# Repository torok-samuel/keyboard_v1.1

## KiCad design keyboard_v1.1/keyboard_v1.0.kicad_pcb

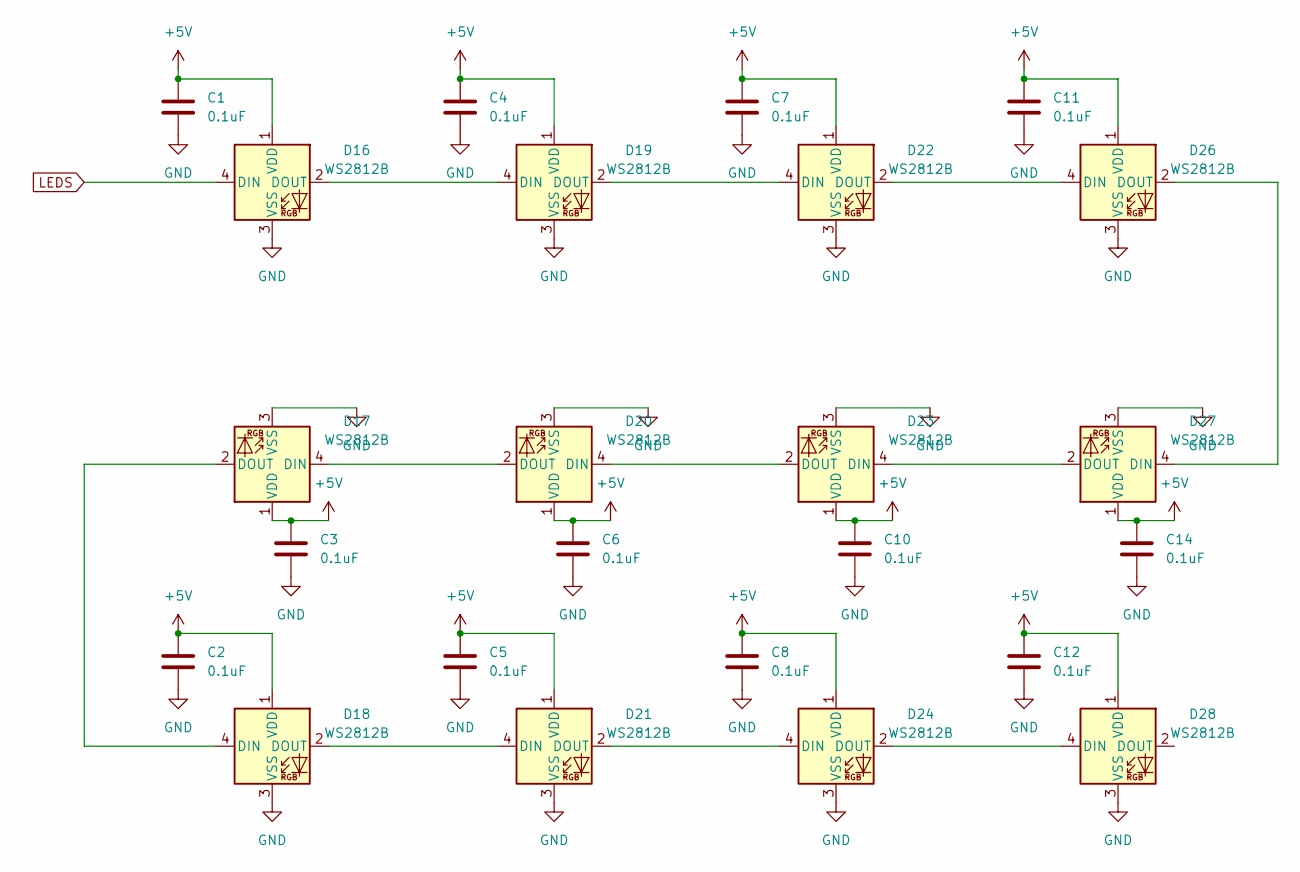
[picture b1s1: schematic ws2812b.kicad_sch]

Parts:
C1, C2, C3, C4, C5, C6, C7, C8, C10, C11, C12, C14: 0.1uF; C_0805_2012Metric_Pad1.18x1.45mm_HandSolder
D16, D17, D18, D19, D20, D21, D22, D23, D24, D26, D27, D28: WS2812B; LED_WS2812B_PLCC4_5.0x5.0mm_P3.2mm

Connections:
5V_OUT: C1.1, C2.1, C3.1, C4.1, C5.1, C6.1, C7.1, C8.1, C10.1, C11.1, C12.1, C14.1, D16.1 (VDD), D17.1 (VDD), D18.1 (VDD), D19.1 (VDD), D20.1 (VDD), D21.1 (VDD), D22.1 (VDD), D23.1 (VDD), D24.1 (VDD), D26.1 (VDD), D27.1 (VDD), D28.1 (VDD); also elsewhere on the board
GND: C1.2, C2.2, C3.2, C4.2, C5.2, C6.2, C7.2, C8.2, C10.2, C11.2, C12.2, C14.2, D16.3 (VSS), D17.3 (VSS), D18.3 (VSS), D19.3 (VSS), D20.3 (VSS), D21.3 (VSS), D22.3 (VSS), D23.3 (VSS), D24.3 (VSS), D26.3 (VSS), D27.3 (VSS), D28.3 (VSS); also elsewhere on the board
LEDS: D16.4 (DIN); also elsewhere on the board
unnamed: D16.2 (DOUT), D19.4 (DIN)
unnamed: D17.2 (DOUT), D18.4 (DIN)
unnamed: D17.4 (DIN), D20.2 (DOUT)
unnamed: D18.2 (DOUT), D21.4 (DIN)
unnamed: D19.2 (DOUT), D22.4 (DIN)
unnamed: D20.4 (DIN), D23.2 (DOUT)
unnamed: D21.2 (DOUT), D24.4 (DIN)
unnamed: D22.2 (DOUT), D26.4 (DIN)
unnamed: D23.4 (DIN), D27.2 (DOUT)
unnamed: D24.2 (DOUT), D28.4 (DIN)
unnamed: D26.2 (DOUT), D27.4 (DIN)

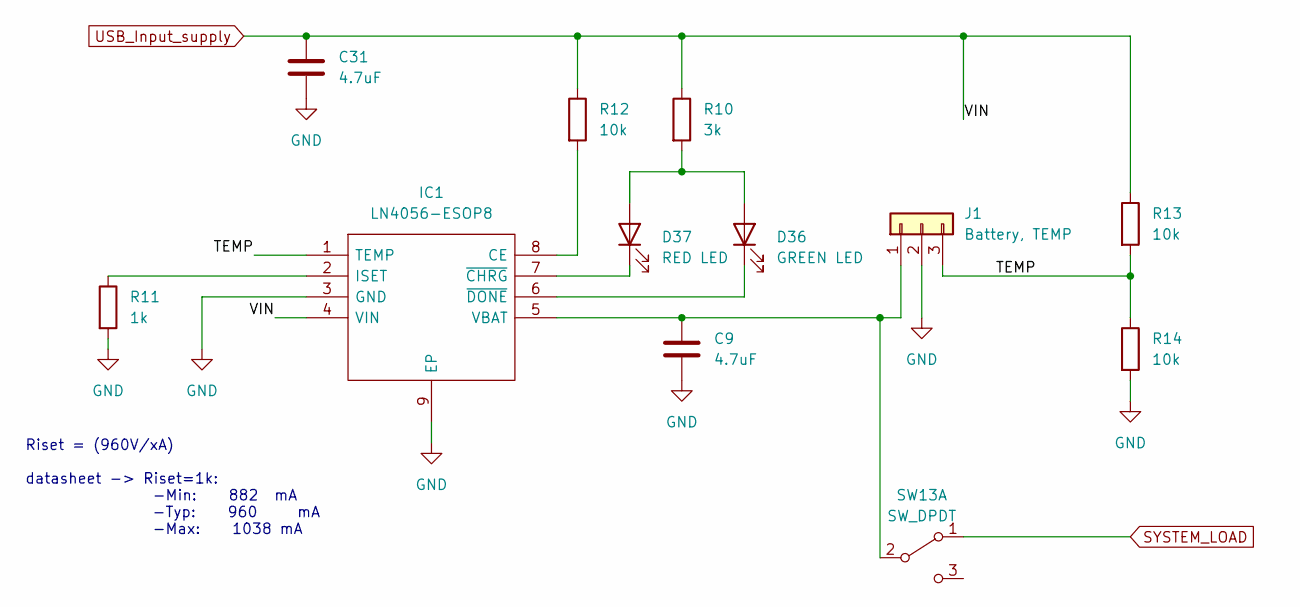
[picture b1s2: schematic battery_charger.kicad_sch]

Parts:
C9, C31: 4.7uF; C_0805_2012Metric_Pad1.18x1.45mm_HandSolder
D36: GREEN LED; LED_0805_2012Metric_Pad1.15x1.40mm_HandSolder
D37: RED LED; LED_0805_2012Metric_Pad1.15x1.40mm_HandSolder
IC1: LN4056-ESOP8; SOIC127P600X175-9N; Manufacturer_Part_Number TP4056-42-ESOP8
J1: Battery, TEMP; PinSocket_1x03_P2.54mm_Horizontal
R10: 3k; R_0805_2012Metric_Pad1.20x1.40mm_HandSolder
R11: 1k; R_0805_2012Metric_Pad1.20x1.40mm_HandSolder
R12, R13, R14: 10k; R_0805_2012Metric_Pad1.20x1.40mm_HandSolder
SW13: SW_DPDT; PinHeader_1x03_P2.54mm_Horizontal

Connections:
/battery_charger/TEMP: IC1.1 (TEMP), J1.3, R13.2, R14.1
GND: C9.2, C31.2, IC1.3 (GND), IC1.9 (EP), J1.2, R11.2, R14.2; also elsewhere on the board
unnamed: C9.1, IC1.5 (VBAT), J1.1, SW13.2 (B)
unnamed: D36.1 (K), IC1.6 (~DONE)
unnamed: D36.2 (A), D37.2 (A), R10.2
unnamed: D37.1 (K), IC1.7 (~CHRG)
unnamed: IC1.2 (ISET), R11.1
unnamed: IC1.8 (CE), R12.2
SYSTEM_LOAD: SW13.1 (A); also elsewhere on the board
USB_Input_supply: C31.1, IC1.4 (VIN), R10.1, R12.1, R13.1; also elsewhere on the board

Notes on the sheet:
Riset = (960V/xA) datasheet -> Riset=1k: -Min: 882 mA -Typ: 960 mA -Max: 1038 mA

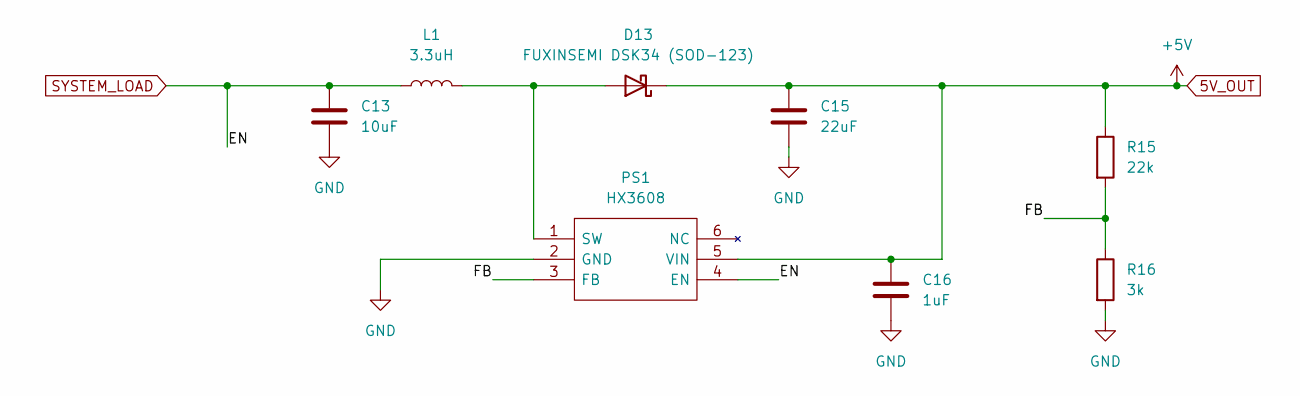
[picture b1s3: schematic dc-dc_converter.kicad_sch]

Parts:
C13: 10uF; C_0805_2012Metric_Pad1.18x1.45mm_HandSolder
C15: 22uF; C_0805_2012Metric_Pad1.18x1.45mm_HandSolder
C16: 1uF; C_0805_2012Metric_Pad1.18x1.45mm_HandSolder
D13: FUXINSEMI DSK34 (SOD-123); D_SOD-123
L1: 3.3uH; inductor_koherelec
PS1: HX3608; SOT95P280X125-6N; Manufacturer_Part_Number HX3608
R15: 22k; R_0805_2012Metric_Pad1.20x1.40mm_HandSolder
R16: 3k; R_0805_2012Metric_Pad1.20x1.40mm_HandSolder

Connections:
5V_OUT: C15.1, C16.1, D13.1 (K), PS1.5 (VIN), R15.1; also elsewhere on the board
/DC-DC_Converters_5V/FB: PS1.3 (FB), R15.2, R16.1
GND: C13.2, C15.2, C16.2, PS1.2 (GND), R16.2; also elsewhere on the board
unnamed: D13.2 (A), L1.2, PS1.1 (SW)
SYSTEM_LOAD: C13.1, L1.1, PS1.4 (EN); also elsewhere on the board

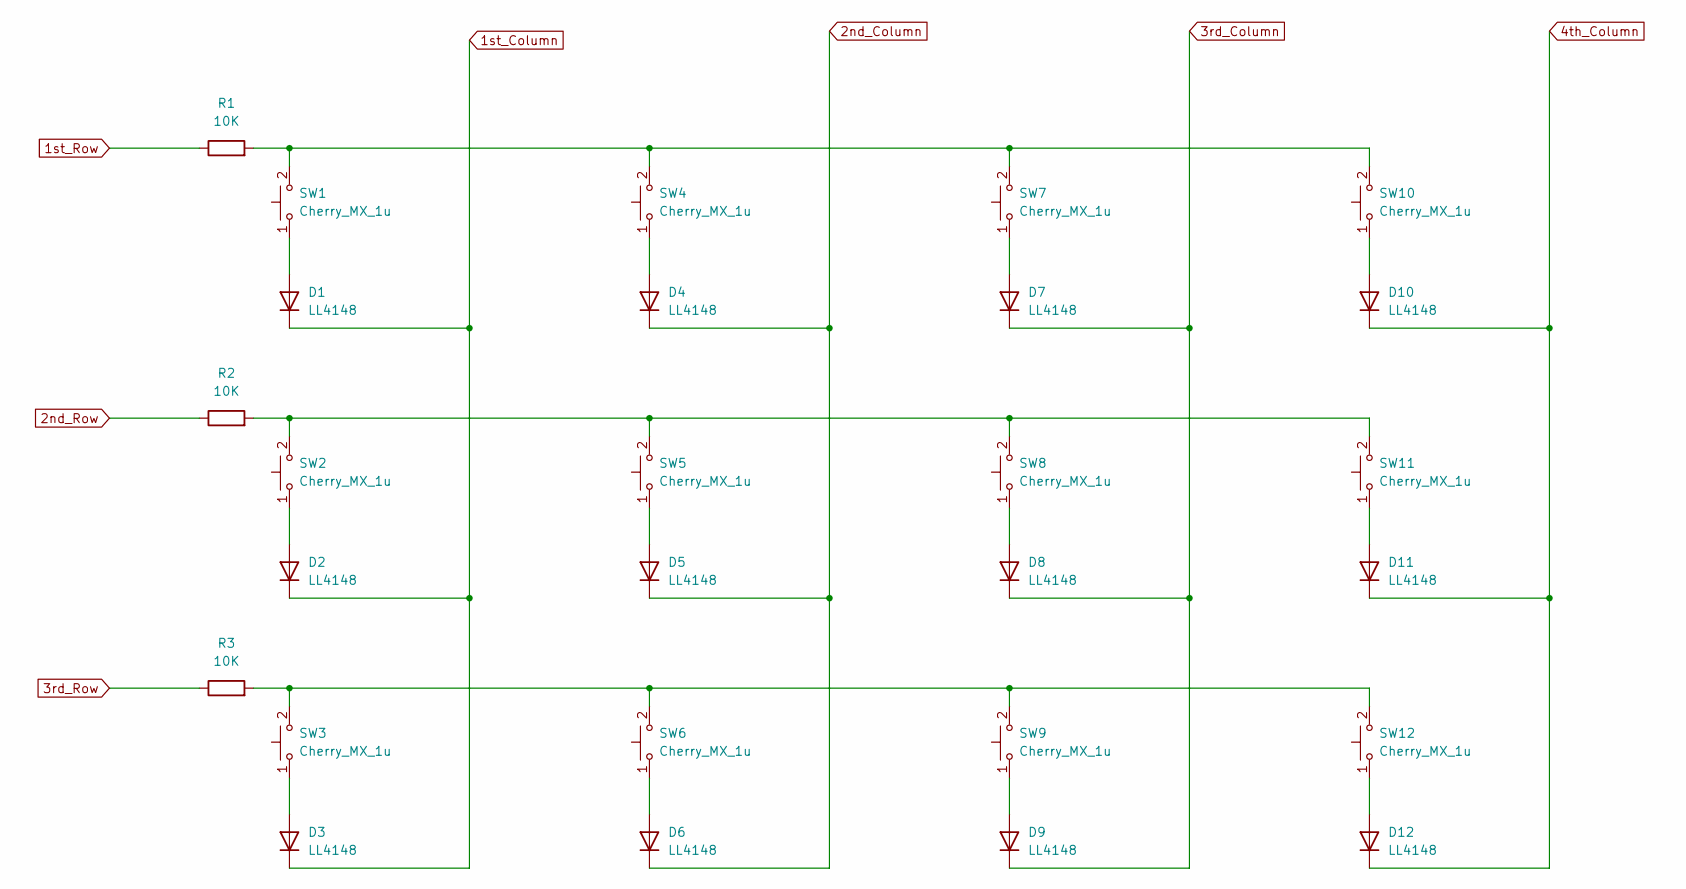
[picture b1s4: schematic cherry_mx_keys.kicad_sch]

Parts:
D1, D2, D3, D4, D5, D6, D7, D8, D9, D10, D11, D12: LL4148; D_MiniMELF
R1, R2, R3: 10K; R_0805_2012Metric_Pad1.20x1.40mm_HandSolder
SW1, SW2, SW3, SW4, SW5, SW6, SW7, SW8, SW9, SW10, SW11, SW12: Cherry_MX_1u; SW_Cherry_MX_PCB_1.00u

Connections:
1st_Column: D1.1 (K), D2.1 (K), D3.1 (K); also elsewhere on the board
1st_Row: R1.1; also elsewhere on the board
2nd_Column: D4.1 (K), D5.1 (K), D6.1 (K); also elsewhere on the board
2nd_Row: R2.1; also elsewhere on the board
3rd_Column: D7.1 (K), D8.1 (K), D9.1 (K); also elsewhere on the board
3rd_Row: R3.1; also elsewhere on the board
4th_Column: D10.1 (K), D11.1 (K), D12.1 (K); also elsewhere on the board
unnamed: D1.2 (A), SW1.1
unnamed: D2.2 (A), SW2.1
unnamed: D3.2 (A), SW3.1
unnamed: D4.2 (A), SW4.1
unnamed: D5.2 (A), SW5.1
unnamed: D6.2 (A), SW6.1
unnamed: D7.2 (A), SW7.1
unnamed: D8.2 (A), SW8.1
unnamed: D9.2 (A), SW9.1
unnamed: D10.2 (A), SW10.1
unnamed: D11.2 (A), SW11.1
unnamed: D12.2 (A), SW12.1
unnamed: R1.2, SW1.2, SW4.2, SW7.2, SW10.2
unnamed: R2.2, SW2.2, SW5.2, SW8.2, SW11.2
unnamed: R3.2, SW3.2, SW6.2, SW9.2, SW12.2

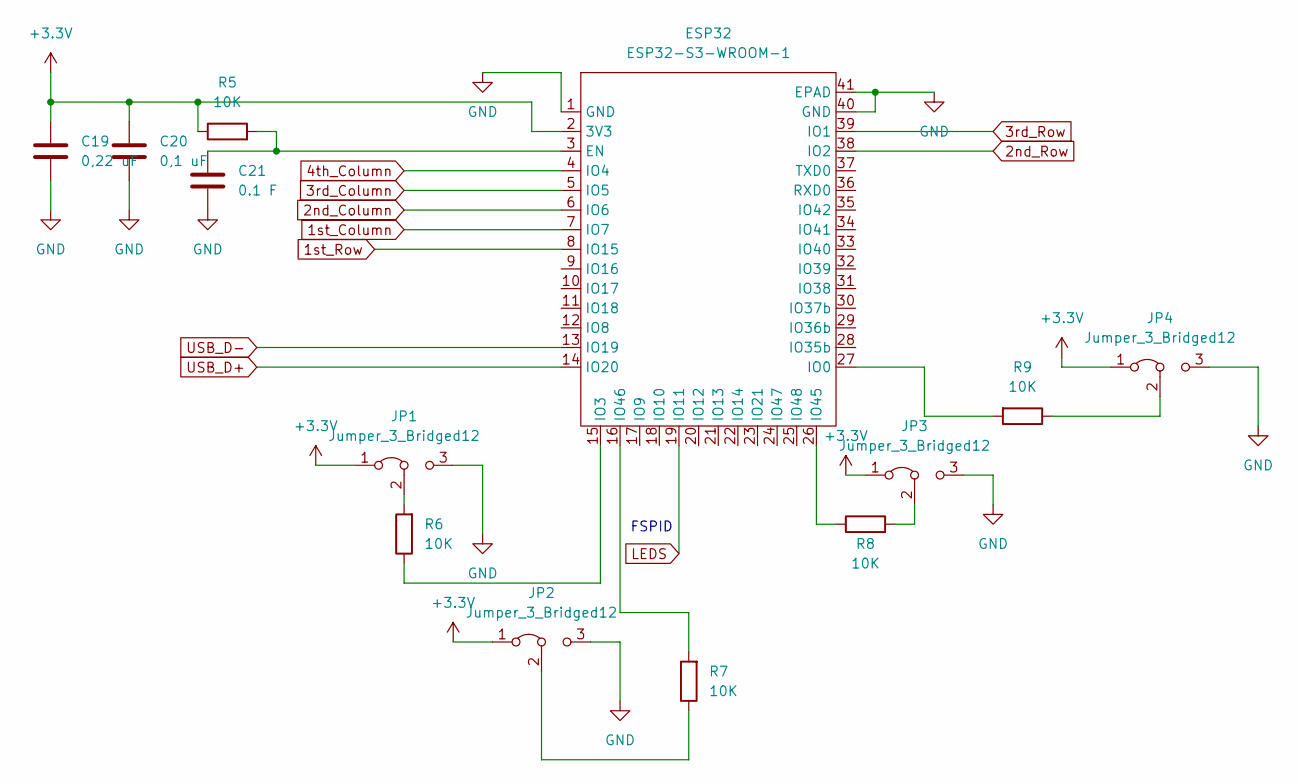
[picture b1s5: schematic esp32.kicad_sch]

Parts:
C19: 0,22 uF; C_0805_2012Metric_Pad1.18x1.45mm_HandSolder
C20: 0,1 uF; C_0805_2012Metric_Pad1.18x1.45mm_HandSolder
C21: 0.1 F; C_0805_2012Metric_Pad1.18x1.45mm_HandSolder
ESP32: ESP32-S3-WROOM-1
JP1, JP2, JP3, JP4: Jumper_3_Bridged12; PinHeader_1x03_P2.54mm_Horizontal
R5, R6, R7, R8, R9: 10K; R_0805_2012Metric_Pad1.20x1.40mm_HandSolder

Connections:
1st_Column: ESP32.7 (IO7); also elsewhere on the board
1st_Row: ESP32.8 (IO15); also elsewhere on the board
2nd_Column: ESP32.6 (IO6); also elsewhere on the board
2nd_Row: ESP32.38 (IO2); also elsewhere on the board
3.3V_OUT: C19.1, C20.1, ESP32.2 (3V3), JP1.1 (A), JP2.1 (A), JP3.1 (A), JP4.1 (A), R5.1; also elsewhere on the board
3rd_Column: ESP32.5 (IO5); also elsewhere on the board
3rd_Row: ESP32.39 (IO1); also elsewhere on the board
4th_Column: ESP32.4 (IO4); also elsewhere on the board
GND: C19.2, C20.2, C21.2, ESP32.1 (GND), ESP32.40 (GND), ESP32.41 (EPAD), JP1.3 (B), JP2.3 (B), JP3.3 (B), JP4.3 (B); also elsewhere on the board
LEDS: ESP32.19 (IO11); also elsewhere on the board
unnamed: C21.1, ESP32.3 (EN), R5.2
unnamed: ESP32.15 (IO3), R6.1
unnamed: ESP32.16 (IO46), R7.2
unnamed: ESP32.26 (IO45), R8.1
unnamed: ESP32.27 (IO0), R9.2
unnamed: JP1.2 (C), R6.2
unnamed: JP2.2 (C), R7.1
unnamed: JP3.2 (C), R8.2
unnamed: JP4.2 (C), R9.1
USB_D+: ESP32.14 (IO20); also elsewhere on the board
USB_D-: ESP32.13 (IO19); also elsewhere on the board

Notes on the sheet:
FSPID

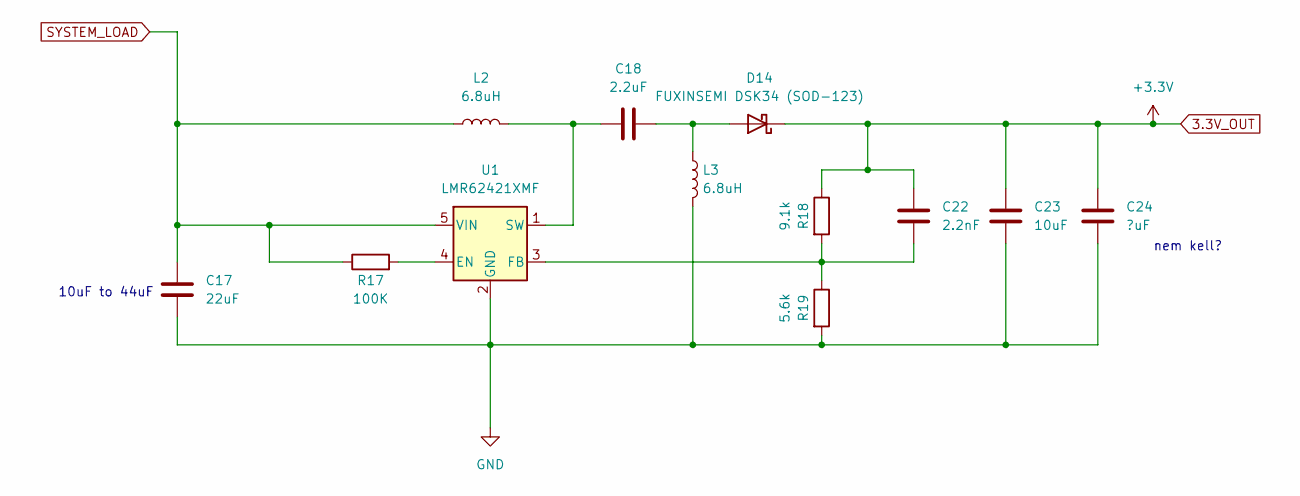
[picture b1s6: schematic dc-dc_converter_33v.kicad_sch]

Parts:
C17: 22uF; C_0805_2012Metric_Pad1.18x1.45mm_HandSolder
C18: 2.2uF; C_0805_2012Metric_Pad1.18x1.45mm_HandSolder
C22: 2.2nF; C_0805_2012Metric_Pad1.18x1.45mm_HandSolder
C23: 10uF; C_0805_2012Metric_Pad1.18x1.45mm_HandSolder
C24: ?uF; C_0805_2012Metric_Pad1.18x1.45mm_HandSolder
D14: FUXINSEMI DSK34 (SOD-123); D_SOD-123
L2, L3: 6.8uH; inductor_koherelec
R17: 100K; R_0805_2012Metric_Pad1.20x1.40mm_HandSolder
R18: 9.1k; R_0805_2012Metric_Pad1.20x1.40mm_HandSolder
R19: 5.6k; R_0805_2012Metric_Pad1.20x1.40mm_HandSolder
U1: LMR62421XMF; SOT-23-5

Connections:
3.3V_OUT: C22.1, C23.1, C24.1, D14.1 (K), R18.1; also elsewhere on the board
GND: C17.2, C23.2, C24.2, L3.2, R19.2, U1.2 (GND); also elsewhere on the board
unnamed: C18.1, L2.2, U1.1 (SW)
unnamed: C18.2, D14.2 (A), L3.1
unnamed: C22.2, R18.2, R19.1, U1.3 (FB)
unnamed: R17.2, U1.4 (EN)
SYSTEM_LOAD: C17.1, L2.1, R17.1, U1.5 (VIN); also elsewhere on the board

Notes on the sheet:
10uF to 44uF
nem kell?

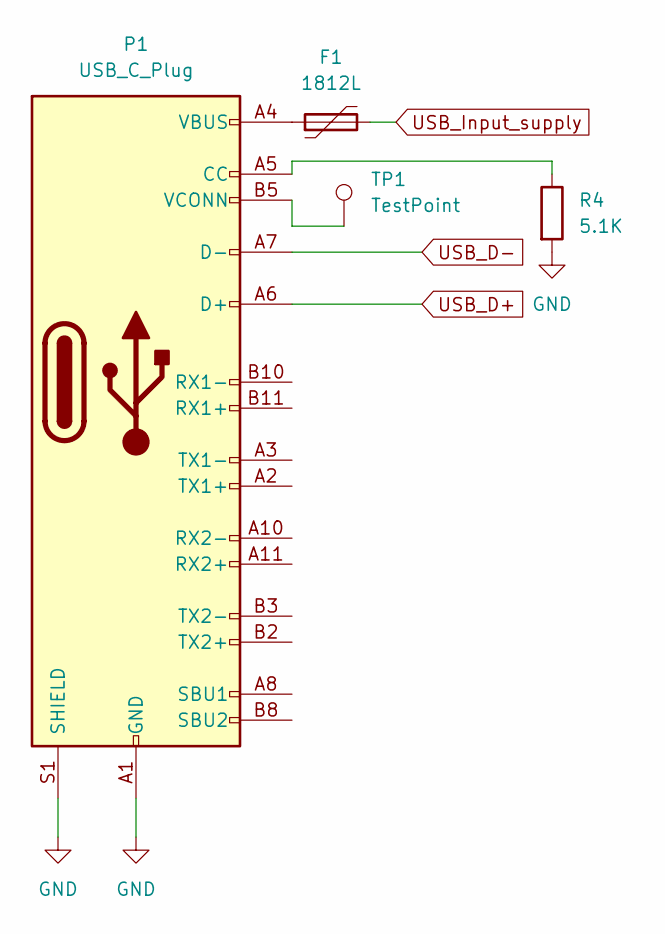
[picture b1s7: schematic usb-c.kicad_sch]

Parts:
F1: 1812L; FUSM4632X200N
P1: USB_C_Plug; USB_C_Receptacle_HRO_TYPE-C-31-M-12
R4: 5.1K; R_0805_2012Metric_Pad1.20x1.40mm_HandSolder
TP1: TestPoint; TestPoint_Keystone_5010-5014_Multipurpose

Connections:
GND: P1.A1 (GND), P1.A12 (GND), P1.B1 (GND), P1.B12 (GND), P1.S1 (SHIELD), R4.2; also elsewhere on the board
unnamed: F1.1, P1.A4 (VBUS), P1.A9 (VBUS), P1.B4 (VBUS), P1.B9 (VBUS)
unnamed: P1.A5 (CC), R4.1
unnamed: P1.B5 (VCONN), TP1.1
USB_D+: P1.A6 (D+); also elsewhere on the board
USB_D-: P1.A7 (D-); also elsewhere on the board
USB_Input_supply: F1.2; also elsewhere on the board

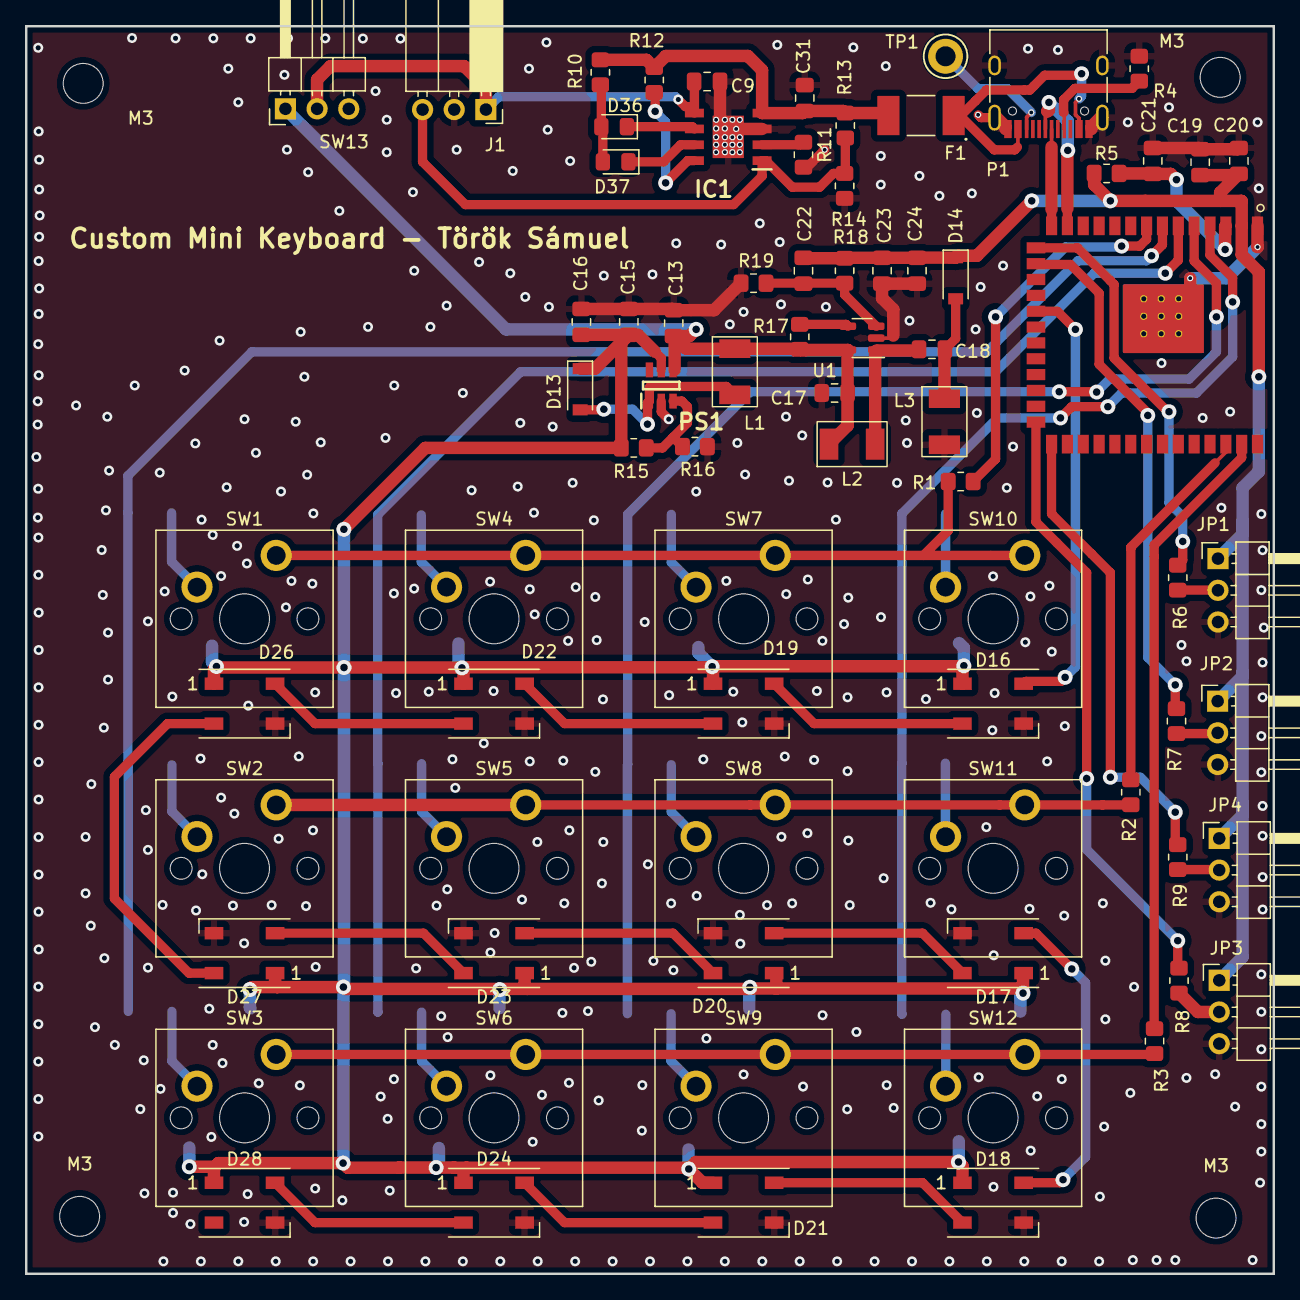
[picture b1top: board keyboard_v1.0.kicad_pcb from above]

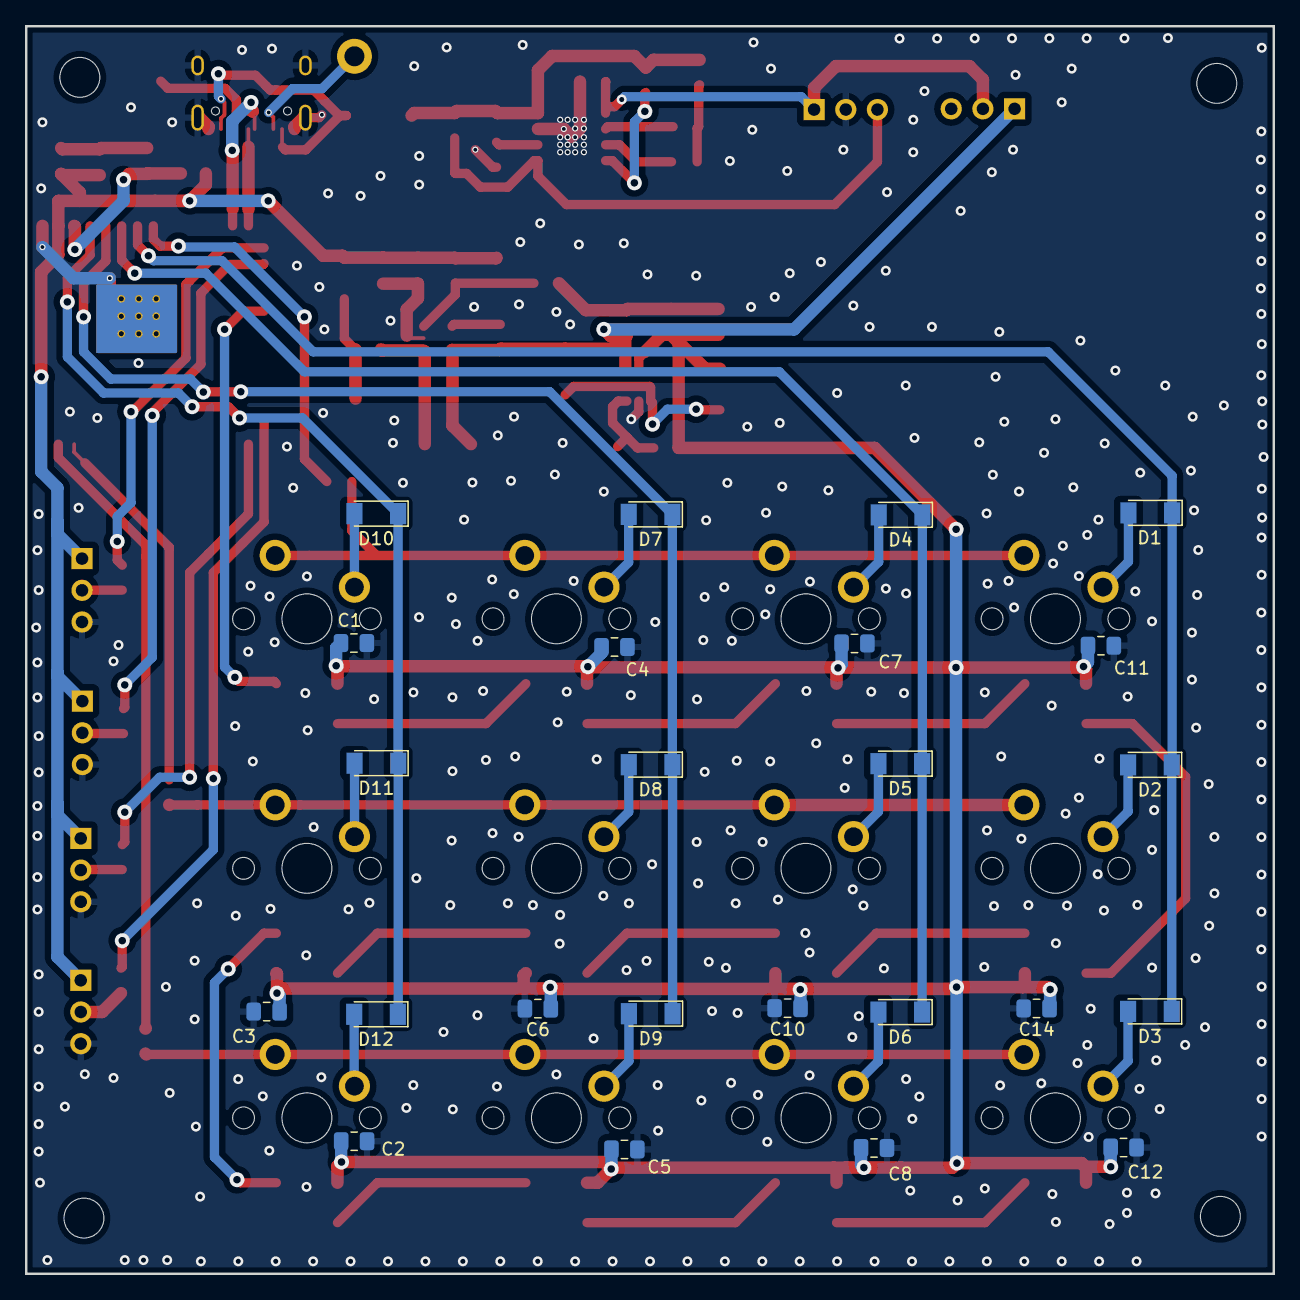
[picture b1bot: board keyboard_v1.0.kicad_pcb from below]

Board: 2 copper layers, 100.0 x 100.0 mm, 104 parts (24 on the bottom side), 66 nets.

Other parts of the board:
M3, M3#2, M3#3, M3#4: MountingHole_3.2mm_M3

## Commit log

2022-04-12 2022-04-12 in the middle of the keyboard_v1.1 pcb design
2022-04-12 2022-04-12 keyboard v1.1 with generated gerber files
2022-04-14 2022-04-14 added vias and led positions
2022-04-21 2022.04.21. 22:45
2022-04-21 2022.04.21. 22:45 gerber2 files added
2022-04-22 2022.04.22. added the sent jlcpcb_gerberfile
2022-07-20 New design - schematics added (2022.07.20.)
2022-07-20 New design - after switch/checkout
2022-07-25 PCB layout done - 2022.07.25.
2022-08-03 Corrections on PCB design - 2022.08.04.
2022-08-03 PCB design corrections and gerber files (jlcpcb_gerberfile_new/) - 2022.08.04.
2022-08-09 Fixing unconnected tracks - 2022.08.09.
2022-12-05 Firmware added
